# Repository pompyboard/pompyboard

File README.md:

# Wonkle

Wonkle builds gaming hardware such as tablets and keypads for gamers.
Source code, 3D models, schematics, etc. are available under
[OSI-Approved Software and Hardware Licenses](https://opensource.org/licenses). We welcome everyone
to contribute and join us in our quest to make the best hardware for our fellow gamers.

## [Frequently Asked Questions](https://docs.wonkle.io/faq.html)

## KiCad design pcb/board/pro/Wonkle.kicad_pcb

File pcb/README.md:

# PCB

Designed with [KiCad][kicad].

## Manufacturing

Both prototype and production PCB is manufactured by [JLCPCB][jlcpcb].

### Steps

1. Install [KiCad][kicad].
2. Install the [Fabrication Toolkit][fab-toolkit] plugin.
3. "Generate" production files using the plugin with default settings.
4. Go to [jlcpcb.com][jlcpcb] and click "Add gerber file"
5. Select `pcb/production/wonkle.zip`
6. Configure PCB (you will get 5 pcb of which 2 have components soldered)
   - PCB Specifications
     - PCB Thickness - 1.0mm
     - Surface Finish - LeadFree HASL (health is important boiz)
   - High-spec Options
     - Confirm Production file - Yes
     - Mark on PCB - Order Number(Specify Position)
   - PCB Assembly
     - PCBA Qty - minimum is 2
     - Confirm Parts Placement - Yes
     - Advanced
       - Board Cleaning - Yes
7. Press "NEXT"
8. Inspect PCB and press "NEXT" again
9. Upload and process `pcb/production/bom.csv` and `pcb/production/positions.csv`
10. Review the parts and press "NEXT"
11. Fix component placement
    - only J2 (1x4 pin) needs manual edit
12. Select `Research\Education\DIY\Entertainment > DIY Hobby Circuit Board - HS Code 902300` in Quote & Order section. The total price is 137.13 USD as of writing.
13. Press "SAVE TO CART"
14. Select both PCB and PCBA then click "Secure Checkout"
15. Enter shipping info and follow JLCPCB's instruction (e.g. production file confirmation)
16. Wait for a week and you'll receive your very own board!

[kicad]: https://www.kicad.org/
[jlcpcb]: https://jlcpcb.com/
[fab-toolkit]: https://github.com/bennymeg/Fabrication-Toolkit

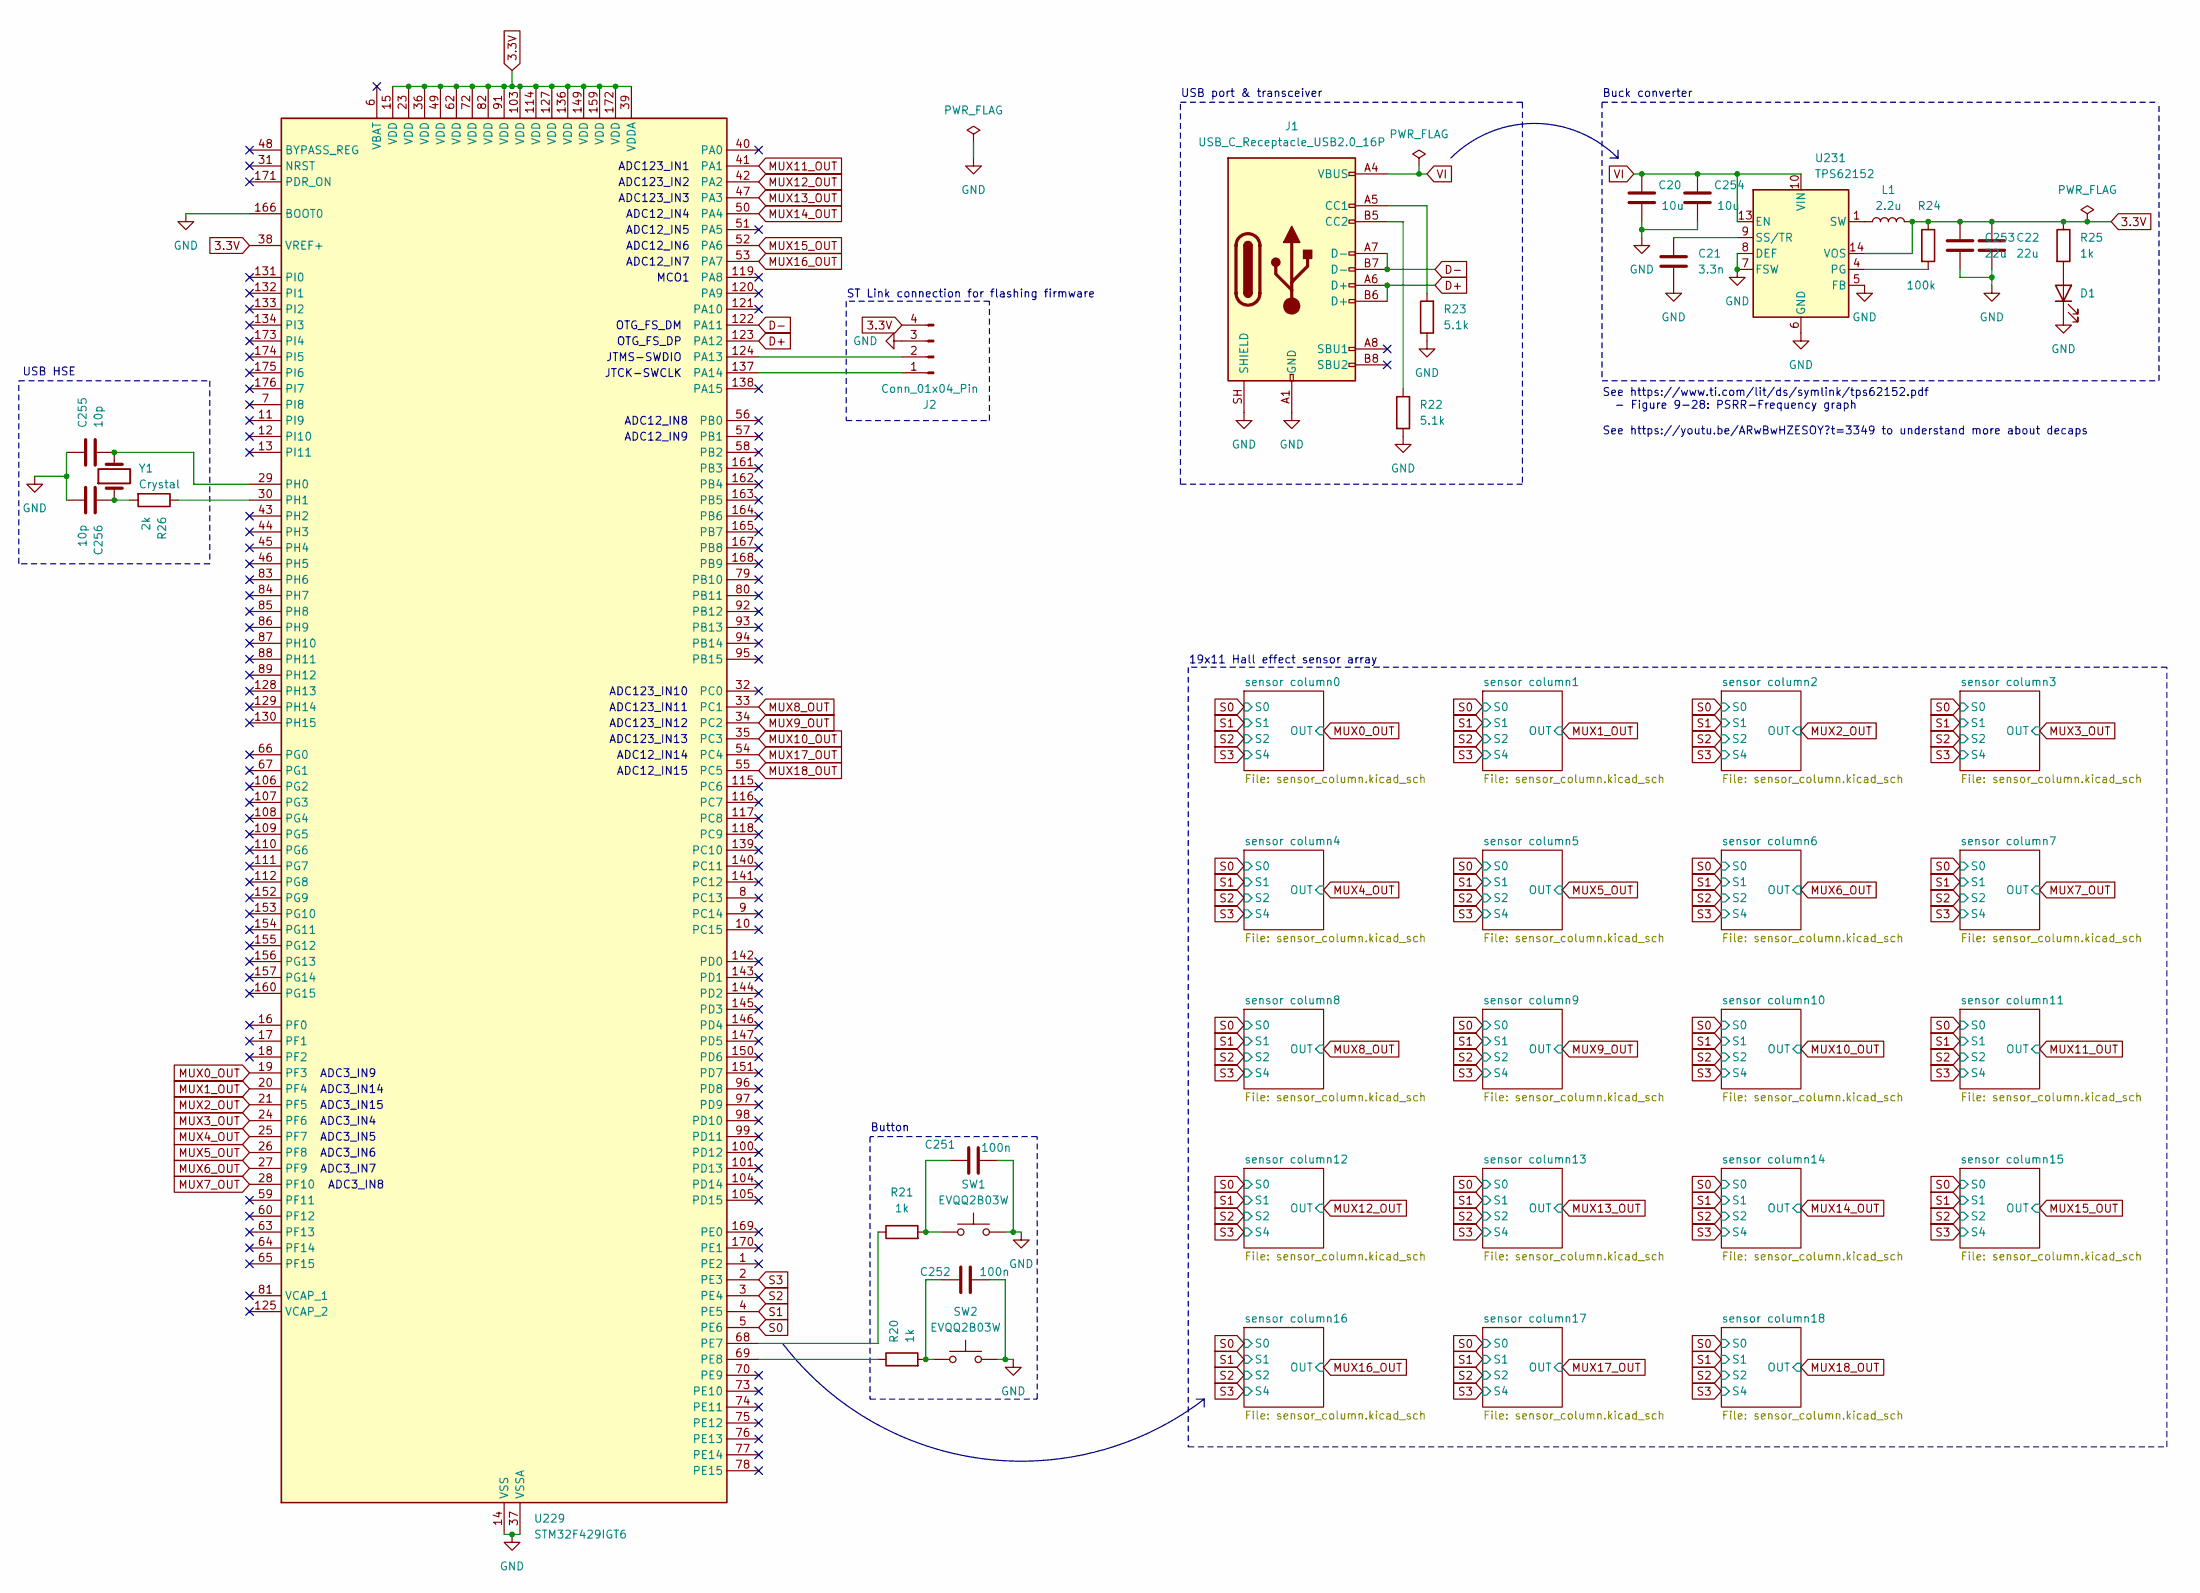
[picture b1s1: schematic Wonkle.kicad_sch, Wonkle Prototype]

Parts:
C20, C254: 10u; C_0402_1005Metric; LCSC Part # C315248
C21: 3.3n; C_0402_1005Metric; LCSC Part # C3881585
C22, C253: 22u; C_0402_1005Metric; LCSC Part # C105226
C251, C252: 100n; C_0402_1005Metric; LCSC Part # C1525
C255, C256: 10p; C_0402_1005Metric; LCSC Part # C1525
D1: F.0603.00139/P2-0603R1TS2-06T-002; LED_0603_1608Metric; LCSC Part # C7496820
J1: USB_C_Receptacle_USB2.0_16P; USB_C_Receptacle_GCT_USB4085; LCSC Part # C7095263
J2: Conn_01x04_Pin; PinHeader_1x04_P2.54mm_Horizontal; LCSC Part # C32713263
L1: 2.2u; L_Coilcraft_XxL4020; LCSC Part # C122469
R20, R21: 1k; R_0402_1005Metric; LCSC Part # C25744
R22, R23: 5.1k; R_0402_1005Metric; LCSC Part # C25905
R24: 100k; R_0603_1608Metric; LCSC Part # C22369815
R25: 1k; R_0402_1005Metric; LCSC Part # C11702
R26: 2k; R_0402_1005Metric; LCSC Part # C11702
SW1, SW2: EVQQ2B03W; SW_SPST_EVQQ2; LCSC Part # C79178
U229: STM32F429IGT6; LQFP-176_24x24mm_P0.5mm
U231: TPS62152; VQFN-16-1EP_3x3mm_P0.5mm_EP1.68x1.68mm_ThermalVias; LCSC Part # C2070611
Y1: Crystal; Crystal_SMD_5032-2Pin_5.0x3.2mm

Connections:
3.3V: C22.1, C253.1, J2.4, L1.2, R24.1, R25.1, U229.15 (VDD), U229.23 (VDD), U229.36 (VDD), U229.38 (VREF+), U229.39 (VDDA), U229.49 (VDD), U229.62 (VDD), U229.72 (VDD), U229.82 (VDD), U229.91 (VDD), U229.103 (VDD), U229.114 (VDD), U229.127 (VDD), U229.136 (VDD), U229.149 (VDD), U229.159 (VDD), U229.172 (VDD), U231.14 (VOS); also elsewhere on the board
D+: J1.A6 (D+), J1.B6 (D+), U229.123 (PA12)
D-: J1.A7 (D-), J1.B7 (D-), U229.122 (PA11)
GND: C20.2, C21.2, C22.2, C251.2, C252.2, C253.2, C254.2, C255.1, C256.2, D1.1 (K), J1.A1 (GND), J1.A12 (GND), J1.B1 (GND), J1.B12 (GND), J1.SH (SHIELD), J2.3, R22.2, R23.1, SW1.2, SW2.2, U229.14 (VSS), U229.22 (VSS), U229.37 (VSSA), U229.61 (VSS), U229.71 (VSS), U229.90 (VSS), U229.102 (VSS), U229.113 (VSS), U229.126 (VSS), U229.135 (VSS), U229.148 (VSS), U229.158 (VSS), U229.166 (BOOT0), U231.5 (FB), U231.6 (GND), U231.7 (FSW), U231.8 (DEF), U231.15 (GND), U231.16 (GND), U231.17 (GND); also elsewhere on the board
MUX0_OUT: U229.19 (PF3); also elsewhere on the board
MUX1_OUT: U229.20 (PF4); also elsewhere on the board
MUX2_OUT: U229.21 (PF5); also elsewhere on the board
MUX3_OUT: U229.24 (PF6); also elsewhere on the board
MUX4_OUT: U229.25 (PF7); also elsewhere on the board
MUX5_OUT: U229.26 (PF8); also elsewhere on the board
MUX6_OUT: U229.27 (PF9); also elsewhere on the board
MUX7_OUT: U229.28 (PF10); also elsewhere on the board
MUX8_OUT: U229.33 (PC1); also elsewhere on the board
MUX9_OUT: U229.34 (PC2); also elsewhere on the board
MUX10_OUT: U229.35 (PC3); also elsewhere on the board
MUX11_OUT: U229.41 (PA1); also elsewhere on the board
MUX12_OUT: U229.42 (PA2); also elsewhere on the board
MUX13_OUT: U229.47 (PA3); also elsewhere on the board
MUX14_OUT: U229.50 (PA4); also elsewhere on the board
MUX15_OUT: U229.52 (PA6); also elsewhere on the board
MUX16_OUT: U229.53 (PA7); also elsewhere on the board
MUX17_OUT: U229.54 (PC4); also elsewhere on the board
MUX18_OUT: U229.55 (PC5); also elsewhere on the board
unnamed: C251.1, R21.2, SW1.1
unnamed: C252.1, R20.2, SW2.1
unnamed: C256.1, R26.2, Y1.1
unnamed: D1.2 (A), R25.2
unnamed: J1.A5 (CC1), R23.2
unnamed: J1.B5 (CC2), R22.1
unnamed: J2.1, U229.137 (PA14)
unnamed: J2.2, U229.124 (PA13)
unnamed: L1.1, U231.1 (SW), U231.2 (SW), U231.3 (SW)
unnamed: R21.1, U229.68 (PE7)
unnamed: R20.1, U229.69 (PE8)
unnamed: C255.2, U229.29 (PH0), Y1.2
unnamed: R26.1, U229.30 (PH1)
unnamed: R24.2, U231.4 (PG)
unnamed: C21.1, U231.9 (SS/TR)
S0: U229.5 (PE6); also elsewhere on the board
S1: U229.4 (PE5); also elsewhere on the board
S2: U229.3 (PE4); also elsewhere on the board
S3: U229.2 (PE3); also elsewhere on the board
VI: C20.1, C254.1, J1.A4 (VBUS), J1.A9 (VBUS), J1.B4 (VBUS), J1.B9 (VBUS), U231.10 (VIN), U231.11 (VIN), U231.12 (VIN), U231.13 (EN)

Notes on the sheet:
ADC3_IN6
ADC3_IN8
ADC12_IN15
ADC3_IN14
ADC12_IN14
ADC123_IN10
ADC123_IN12
Button
ADC12_IN9
ADC3_IN15
OTG_FS_DM
ADC3_IN4
See https://www.ti.com/lit/ds/symlink/tps62152.pdf - Figure 9-28: PSRR-Frequency graph See https://youtu.be/ARwBwHZESOY?t=3349 to understand more about decaps
USB HSE
ADC12_IN4
Buck converter
19x11 Hall effect sensor array
ADC3_IN9
ADC123_IN1
ADC123_IN13
ADC12_IN6
ADC3_IN5
ADC12_IN5
ST Link connection for flashing firmware
JTCK-SWCLK
USB port & transceiver
OTG_FS_DP
MCO1
ADC123_IN11
ADC12_IN8
ADC12_IN7
JTMS-SWDIO
ADC123_IN3
ADC123_IN2
ADC3_IN7

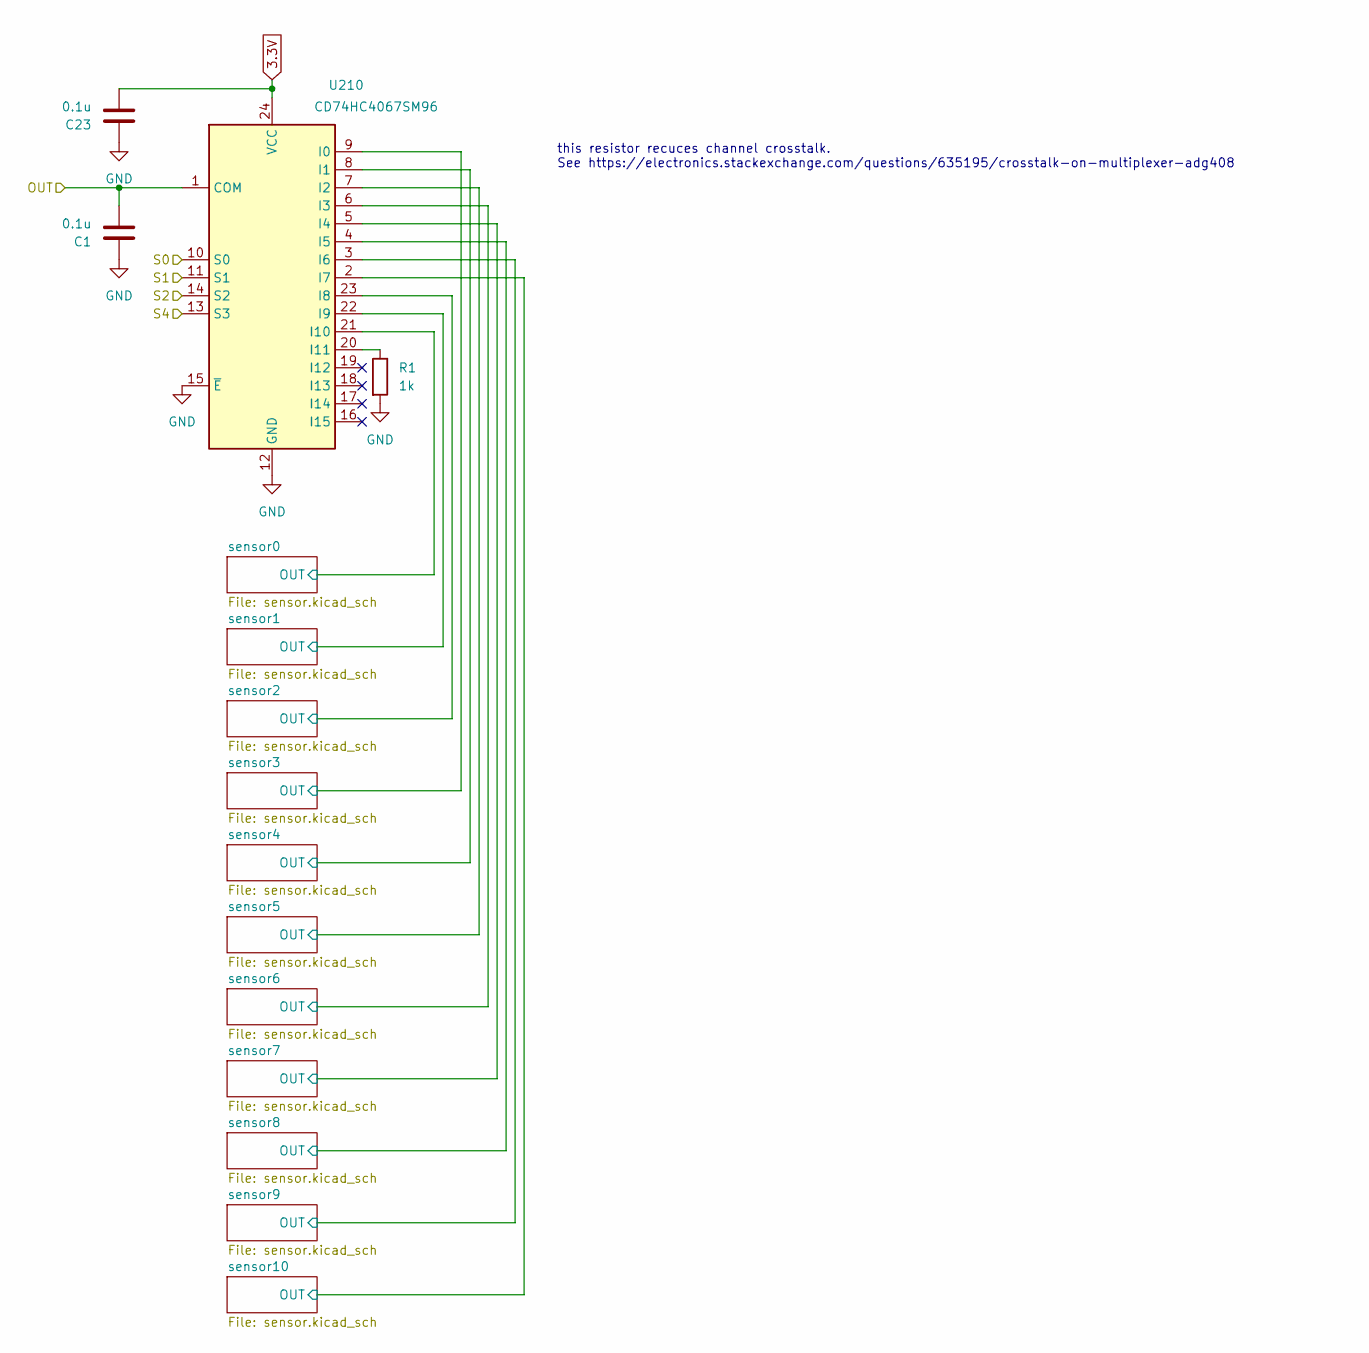
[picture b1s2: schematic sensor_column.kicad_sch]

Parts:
C1, C23: 0.1u; C_0402_1005Metric; LCSC Part # C1525
R1: 1k; R_0402_1005Metric; LCSC Part # C11702
U210: CD74HC4067SM96; SSOP-24_5.3x8.2mm_P0.65mm

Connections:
3.3V: C23.2, U210.24 (VCC); also elsewhere on the board
/sensor column0/sensor0/OUT: U210.21 (I10); also elsewhere on the board
/sensor column0/sensor1/OUT: U210.22 (I9); also elsewhere on the board
/sensor column0/sensor2/OUT: U210.23 (I8); also elsewhere on the board
/sensor column0/sensor3/OUT: U210.9 (I0); also elsewhere on the board
/sensor column0/sensor4/OUT: U210.8 (I1); also elsewhere on the board
/sensor column0/sensor5/OUT: U210.7 (I2); also elsewhere on the board
/sensor column0/sensor6/OUT: U210.6 (I3); also elsewhere on the board
/sensor column0/sensor7/OUT: U210.5 (I4); also elsewhere on the board
/sensor column0/sensor8/OUT: U210.4 (I5); also elsewhere on the board
/sensor column0/sensor9/OUT: U210.3 (I6); also elsewhere on the board
/sensor column0/sensor10/OUT: U210.2 (I7); also elsewhere on the board
GND: C1.1, C23.1, R1.2, U210.12 (GND), U210.15 (~E); also elsewhere on the board
MUX0_OUT: C1.2, U210.1 (COM); also elsewhere on the board
unnamed: R1.1, U210.20 (I11)
S0: U210.10 (S0); also elsewhere on the board
S1: U210.11 (S1); also elsewhere on the board
S2: U210.14 (S2); also elsewhere on the board
S3: U210.13 (S3); also elsewhere on the board

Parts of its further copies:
C2, C3, C4, C5, C6, C7, C8, C9, C10, C11, C12, C13, C14, C15, C16, C17, C18, C19, C24, C25, C26, C27, C28, C29, C30, C31, C32, C33, C34, C35, C36, C37, C38, C39, C40, C41: 0.1u; C_0402_1005Metric; LCSC Part # C1525
R2, R3, R4, R5, R6, R7, R8, R9, R10, R11, R12, R13, R14, R15, R16, R17, R18, R19: 1k; R_0402_1005Metric; LCSC Part # C11702
U211, U212, U213, U214, U215, U216, U217, U218, U219, U220, U221, U222, U223, U224, U225, U226, U227, U228: CD74HC4067SM96; SSOP-24_5.3x8.2mm_P0.65mm

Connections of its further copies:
3.3V: C24.2, C25.2, C26.2, C27.2, C28.2, C29.2, C30.2, C31.2, C32.2, C33.2, C34.2, C35.2, C36.2, C37.2, C38.2, C39.2, C40.2, C41.2, U211.24 (VCC), U212.24 (VCC), U213.24 (VCC), U214.24 (VCC), U215.24 (VCC), U216.24 (VCC), U217.24 (VCC), U218.24 (VCC), U219.24 (VCC), U220.24 (VCC), U221.24 (VCC), U222.24 (VCC), U223.24 (VCC), U224.24 (VCC), U225.24 (VCC), U226.24 (VCC), U227.24 (VCC), U228.24 (VCC); also elsewhere on the board
/sensor column1/sensor0/OUT: U211.21 (I10); also elsewhere on the board
/sensor column1/sensor1/OUT: U211.22 (I9); also elsewhere on the board
/sensor column1/sensor2/OUT: U211.23 (I8); also elsewhere on the board
/sensor column1/sensor3/OUT: U211.9 (I0); also elsewhere on the board
/sensor column1/sensor4/OUT: U211.8 (I1); also elsewhere on the board
/sensor column1/sensor5/OUT: U211.7 (I2); also elsewhere on the board
/sensor column1/sensor6/OUT: U211.6 (I3); also elsewhere on the board
/sensor column1/sensor7/OUT: U211.5 (I4); also elsewhere on the board
/sensor column1/sensor8/OUT: U211.4 (I5); also elsewhere on the board
/sensor column1/sensor9/OUT: U211.3 (I6); also elsewhere on the board
/sensor column1/sensor10/OUT: U211.2 (I7); also elsewhere on the board
/sensor column2/sensor0/OUT: U212.21 (I10); also elsewhere on the board
/sensor column2/sensor1/OUT: U212.22 (I9); also elsewhere on the board
/sensor column2/sensor2/OUT: U212.23 (I8); also elsewhere on the board
/sensor column2/sensor3/OUT: U212.9 (I0); also elsewhere on the board
/sensor column2/sensor4/OUT: U212.8 (I1); also elsewhere on the board
/sensor column2/sensor5/OUT: U212.7 (I2); also elsewhere on the board
/sensor column2/sensor6/OUT: U212.6 (I3); also elsewhere on the board
/sensor column2/sensor7/OUT: U212.5 (I4); also elsewhere on the board
/sensor column2/sensor8/OUT: U212.4 (I5); also elsewhere on the board
/sensor column2/sensor9/OUT: U212.3 (I6); also elsewhere on the board
/sensor column2/sensor10/OUT: U212.2 (I7); also elsewhere on the board
/sensor column3/sensor0/OUT: U213.21 (I10); also elsewhere on the board
/sensor column3/sensor1/OUT: U213.22 (I9); also elsewhere on the board
/sensor column3/sensor2/OUT: U213.23 (I8); also elsewhere on the board
/sensor column3/sensor3/OUT: U213.9 (I0); also elsewhere on the board
/sensor column3/sensor4/OUT: U213.8 (I1); also elsewhere on the board
/sensor column3/sensor5/OUT: U213.7 (I2); also elsewhere on the board
/sensor column3/sensor6/OUT: U213.6 (I3); also elsewhere on the board
/sensor column3/sensor7/OUT: U213.5 (I4); also elsewhere on the board
/sensor column3/sensor8/OUT: U213.4 (I5); also elsewhere on the board
/sensor column3/sensor9/OUT: U213.3 (I6); also elsewhere on the board
/sensor column3/sensor10/OUT: U213.2 (I7); also elsewhere on the board
/sensor column4/sensor0/OUT: U214.21 (I10); also elsewhere on the board
/sensor column4/sensor1/OUT: U214.22 (I9); also elsewhere on the board
/sensor column4/sensor2/OUT: U214.23 (I8); also elsewhere on the board
/sensor column4/sensor3/OUT: U214.9 (I0); also elsewhere on the board
/sensor column4/sensor4/OUT: U214.8 (I1); also elsewhere on the board
/sensor column4/sensor5/OUT: U214.7 (I2); also elsewhere on the board
/sensor column4/sensor6/OUT: U214.6 (I3); also elsewhere on the board
/sensor column4/sensor7/OUT: U214.5 (I4); also elsewhere on the board
/sensor column4/sensor8/OUT: U214.4 (I5); also elsewhere on the board
/sensor column4/sensor9/OUT: U214.3 (I6); also elsewhere on the board
/sensor column4/sensor10/OUT: U214.2 (I7); also elsewhere on the board
/sensor column5/sensor0/OUT: U215.21 (I10); also elsewhere on the board
/sensor column5/sensor1/OUT: U215.22 (I9); also elsewhere on the board
/sensor column5/sensor2/OUT: U215.23 (I8); also elsewhere on the board
/sensor column5/sensor3/OUT: U215.9 (I0); also elsewhere on the board
/sensor column5/sensor4/OUT: U215.8 (I1); also elsewhere on the board
/sensor column5/sensor5/OUT: U215.7 (I2); also elsewhere on the board
/sensor column5/sensor6/OUT: U215.6 (I3); also elsewhere on the board
/sensor column5/sensor7/OUT: U215.5 (I4); also elsewhere on the board
/sensor column5/sensor8/OUT: U215.4 (I5); also elsewhere on the board
/sensor column5/sensor9/OUT: U215.3 (I6); also elsewhere on the board
/sensor column5/sensor10/OUT: U215.2 (I7); also elsewhere on the board
/sensor column6/sensor0/OUT: U216.21 (I10); also elsewhere on the board
/sensor column6/sensor1/OUT: U216.22 (I9); also elsewhere on the board
/sensor column6/sensor2/OUT: U216.23 (I8); also elsewhere on the board
/sensor column6/sensor3/OUT: U216.9 (I0); also elsewhere on the board
/sensor column6/sensor4/OUT: U216.8 (I1); also elsewhere on the board
/sensor column6/sensor5/OUT: U216.7 (I2); also elsewhere on the board
/sensor column6/sensor6/OUT: U216.6 (I3); also elsewhere on the board
/sensor column6/sensor7/OUT: U216.5 (I4); also elsewhere on the board
/sensor column6/sensor8/OUT: U216.4 (I5); also elsewhere on the board
/sensor column6/sensor9/OUT: U216.3 (I6); also elsewhere on the board
/sensor column6/sensor10/OUT: U216.2 (I7); also elsewhere on the board
/sensor column7/sensor0/OUT: U217.21 (I10); also elsewhere on the board
/sensor column7/sensor1/OUT: U217.22 (I9); also elsewhere on the board
/sensor column7/sensor2/OUT: U217.23 (I8); also elsewhere on the board
/sensor column7/sensor3/OUT: U217.9 (I0); also elsewhere on the board
/sensor column7/sensor4/OUT: U217.8 (I1); also elsewhere on the board
/sensor column7/sensor5/OUT: U217.7 (I2); also elsewhere on the board
/sensor column7/sensor6/OUT: U217.6 (I3); also elsewhere on the board
/sensor column7/sensor7/OUT: U217.5 (I4); also elsewhere on the board
/sensor column7/sensor8/OUT: U217.4 (I5); also elsewhere on the board
/sensor column7/sensor9/OUT: U217.3 (I6); also elsewhere on the board
/sensor column7/sensor10/OUT: U217.2 (I7); also elsewhere on the board
/sensor column8/sensor0/OUT: U218.21 (I10); also elsewhere on the board
/sensor column8/sensor1/OUT: U218.22 (I9); also elsewhere on the board
/sensor column8/sensor2/OUT: U218.23 (I8); also elsewhere on the board
/sensor column8/sensor3/OUT: U218.9 (I0); also elsewhere on the board
/sensor column8/sensor4/OUT: U218.8 (I1); also elsewhere on the board
/sensor column8/sensor5/OUT: U218.7 (I2); also elsewhere on the board
/sensor column8/sensor6/OUT: U218.6 (I3); also elsewhere on the board
/sensor column8/sensor7/OUT: U218.5 (I4); also elsewhere on the board
/sensor column8/sensor8/OUT: U218.4 (I5); also elsewhere on the board
/sensor column8/sensor9/OUT: U218.3 (I6); also elsewhere on the board
/sensor column8/sensor10/OUT: U218.2 (I7); also elsewhere on the board
/sensor column9/sensor0/OUT: U219.21 (I10); also elsewhere on the board
/sensor column9/sensor1/OUT: U219.22 (I9); also elsewhere on the board
/sensor column9/sensor2/OUT: U219.23 (I8); also elsewhere on the board
/sensor column9/sensor3/OUT: U219.9 (I0); also elsewhere on the board
/sensor column9/sensor4/OUT: U219.8 (I1); also elsewhere on the board
/sensor column9/sensor5/OUT: U219.7 (I2); also elsewhere on the board
/sensor column9/sensor6/OUT: U219.6 (I3); also elsewhere on the board
/sensor column9/sensor7/OUT: U219.5 (I4); also elsewhere on the board
/sensor column9/sensor8/OUT: U219.4 (I5); also elsewhere on the board
/sensor column9/sensor9/OUT: U219.3 (I6); also elsewhere on the board
/sensor column9/sensor10/OUT: U219.2 (I7); also elsewhere on the board
/sensor column10/sensor0/OUT: U220.21 (I10); also elsewhere on the board
/sensor column10/sensor1/OUT: U220.22 (I9); also elsewhere on the board
/sensor column10/sensor2/OUT: U220.23 (I8); also elsewhere on the board
/sensor column10/sensor3/OUT: U220.9 (I0); also elsewhere on the board
/sensor column10/sensor4/OUT: U220.8 (I1); also elsewhere on the board
/sensor column10/sensor5/OUT: U220.7 (I2); also elsewhere on the board
/sensor column10/sensor6/OUT: U220.6 (I3); also elsewhere on the board
/sensor column10/sensor7/OUT: U220.5 (I4); also elsewhere on the board
/sensor column10/sensor8/OUT: U220.4 (I5); also elsewhere on the board
/sensor column10/sensor9/OUT: U220.3 (I6); also elsewhere on the board
/sensor column10/sensor10/OUT: U220.2 (I7); also elsewhere on the board
/sensor column11/sensor0/OUT: U221.21 (I10); also elsewhere on the board
/sensor column11/sensor1/OUT: U221.22 (I9); also elsewhere on the board
/sensor column11/sensor2/OUT: U221.23 (I8); also elsewhere on the board
/sensor column11/sensor3/OUT: U221.9 (I0); also elsewhere on the board
/sensor column11/sensor4/OUT: U221.8 (I1); also elsewhere on the board
/sensor column11/sensor5/OUT: U221.7 (I2); also elsewhere on the board
/sensor column11/sensor6/OUT: U221.6 (I3); also elsewhere on the board
/sensor column11/sensor7/OUT: U221.5 (I4); also elsewhere on the board
/sensor column11/sensor8/OUT: U221.4 (I5); also elsewhere on the board
/sensor column11/sensor9/OUT: U221.3 (I6); also elsewhere on the board
/sensor column11/sensor10/OUT: U221.2 (I7); also elsewhere on the board
/sensor column12/sensor0/OUT: U222.21 (I10); also elsewhere on the board
/sensor column12/sensor1/OUT: U222.22 (I9); also elsewhere on the board
/sensor column12/sensor2/OUT: U222.23 (I8); also elsewhere on the board
/sensor column12/sensor3/OUT: U222.9 (I0); also elsewhere on the board
/sensor column12/sensor4/OUT: U222.8 (I1); also elsewhere on the board
/sensor column12/sensor5/OUT: U222.7 (I2); also elsewhere on the board
/sensor column12/sensor6/OUT: U222.6 (I3); also elsewhere on the board
/sensor column12/sensor7/OUT: U222.5 (I4); also elsewhere on the board
/sensor column12/sensor8/OUT: U222.4 (I5); also elsewhere on the board
/sensor column12/sensor9/OUT: U222.3 (I6); also elsewhere on the board
/sensor column12/sensor10/OUT: U222.2 (I7); also elsewhere on the board
/sensor column13/sensor0/OUT: U223.21 (I10); also elsewhere on the board
/sensor column13/sensor1/OUT: U223.22 (I9); also elsewhere on the board
/sensor column13/sensor2/OUT: U223.23 (I8); also elsewhere on the board
/sensor column13/sensor3/OUT: U223.9 (I0); also elsewhere on the board
/sensor column13/sensor4/OUT: U223.8 (I1); also elsewhere on the board
/sensor column13/sensor5/OUT: U223.7 (I2); also elsewhere on the board
/sensor column13/sensor6/OUT: U223.6 (I3); also elsewhere on the board
/sensor column13/sensor7/OUT: U223.5 (I4); also elsewhere on the board
/sensor column13/sensor8/OUT: U223.4 (I5); also elsewhere on the board
/sensor column13/sensor9/OUT: U223.3 (I6); also elsewhere on the board
/sensor column13/sensor10/OUT: U223.2 (I7); also elsewhere on the board
/sensor column14/sensor0/OUT: U224.21 (I10); also elsewhere on the board
/sensor column14/sensor1/OUT: U224.22 (I9); also elsewhere on the board
/sensor column14/sensor2/OUT: U224.23 (I8); also elsewhere on the board
/sensor column14/sensor3/OUT: U224.9 (I0); also elsewhere on the board
/sensor column14/sensor4/OUT: U224.8 (I1); also elsewhere on the board
/sensor column14/sensor5/OUT: U224.7 (I2); also elsewhere on the board
/sensor column14/sensor6/OUT: U224.6 (I3); also elsewhere on the board
/sensor column14/sensor7/OUT: U224.5 (I4); also elsewhere on the board
/sensor column14/sensor8/OUT: U224.4 (I5); also elsewhere on the board
/sensor column14/sensor9/OUT: U224.3 (I6); also elsewhere on the board
/sensor column14/sensor10/OUT: U224.2 (I7); also elsewhere on the board
/sensor column15/sensor0/OUT: U225.21 (I10); also elsewhere on the board
/sensor column15/sensor1/OUT: U225.22 (I9); also elsewhere on the board
/sensor column15/sensor2/OUT: U225.23 (I8); also elsewhere on the board
/sensor column15/sensor3/OUT: U225.9 (I0); also elsewhere on the board
/sensor column15/sensor4/OUT: U225.8 (I1); also elsewhere on the board
/sensor column15/sensor5/OUT: U225.7 (I2); also elsewhere on the board
/sensor column15/sensor6/OUT: U225.6 (I3); also elsewhere on the board
/sensor column15/sensor7/OUT: U225.5 (I4); also elsewhere on the board
/sensor column15/sensor8/OUT: U225.4 (I5); also elsewhere on the board
/sensor column15/sensor9/OUT: U225.3 (I6); also elsewhere on the board
/sensor column15/sensor10/OUT: U225.2 (I7); also elsewhere on the board
/sensor column16/sensor0/OUT: U226.21 (I10); also elsewhere on the board
/sensor column16/sensor1/OUT: U226.22 (I9); also elsewhere on the board
/sensor column16/sensor2/OUT: U226.23 (I8); also elsewhere on the board
/sensor column16/sensor3/OUT: U226.9 (I0); also elsewhere on the board
/sensor column16/sensor4/OUT: U226.8 (I1); also elsewhere on the board
/sensor column16/sensor5/OUT: U226.7 (I2); also elsewhere on the board
/sensor column16/sensor6/OUT: U226.6 (I3); also elsewhere on the board
/sensor column16/sensor7/OUT: U226.5 (I4); also elsewhere on the board
/sensor column16/sensor8/OUT: U226.4 (I5); also elsewhere on the board
/sensor column16/sensor9/OUT: U226.3 (I6); also elsewhere on the board
/sensor column16/sensor10/OUT: U226.2 (I7); also elsewhere on the board
/sensor column17/sensor0/OUT: U227.21 (I10); also elsewhere on the board
/sensor column17/sensor1/OUT: U227.22 (I9); also elsewhere on the board
/sensor column17/sensor2/OUT: U227.23 (I8); also elsewhere on the board
/sensor column17/sensor3/OUT: U227.9 (I0); also elsewhere on the board
/sensor column17/sensor4/OUT: U227.8 (I1); also elsewhere on the board
/sensor column17/sensor5/OUT: U227.7 (I2); also elsewhere on the board
/sensor column17/sensor6/OUT: U227.6 (I3); also elsewhere on the board
/sensor column17/sensor7/OUT: U227.5 (I4); also elsewhere on the board
/sensor column17/sensor8/OUT: U227.4 (I5); also elsewhere on the board
/sensor column17/sensor9/OUT: U227.3 (I6); also elsewhere on the board
/sensor column17/sensor10/OUT: U227.2 (I7); also elsewhere on the board
/sensor column18/sensor0/OUT: U228.21 (I10); also elsewhere on the board
/sensor column18/sensor1/OUT: U228.22 (I9); also elsewhere on the board
/sensor column18/sensor2/OUT: U228.23 (I8); also elsewhere on the board
/sensor column18/sensor3/OUT: U228.9 (I0); also elsewhere on the board
/sensor column18/sensor4/OUT: U228.8 (I1); also elsewhere on the board
/sensor column18/sensor5/OUT: U228.7 (I2); also elsewhere on the board
/sensor column18/sensor6/OUT: U228.6 (I3); also elsewhere on the board
/sensor column18/sensor7/OUT: U228.5 (I4); also elsewhere on the board
/sensor column18/sensor8/OUT: U228.4 (I5); also elsewhere on the board
/sensor column18/sensor9/OUT: U228.3 (I6); also elsewhere on the board
/sensor column18/sensor10/OUT: U228.2 (I7); also elsewhere on the board
GND: C2.1, C3.1, C4.1, C5.1, C6.1, C7.1, C8.1, C9.1, C10.1, C11.1, C12.1, C13.1, C14.1, C15.1, C16.1, C17.1, C18.1, C19.1, C24.1, C25.1, C26.1, C27.1, C28.1, C29.1, C30.1, C31.1, C32.1, C33.1, C34.1, C35.1, C36.1, C37.1, C38.1, C39.1, C40.1, C41.1, R2.2, R3.2, R4.2, R5.2, R6.2, R7.2, R8.2, R9.2, R10.2, R11.2, R12.2, R13.2, R14.2, R15.2, R16.2, R17.2, R18.2, R19.2, U211.12 (GND), U211.15 (~E), U212.12 (GND), U212.15 (~E), U213.12 (GND), U213.15 (~E), U214.12 (GND), U214.15 (~E), U215.12 (GND), U215.15 (~E), U216.12 (GND), U216.15 (~E), U217.12 (GND), U217.15 (~E), U218.12 (GND), U218.15 (~E), U219.12 (GND), U219.15 (~E), U220.12 (GND), U220.15 (~E), U221.12 (GND), U221.15 (~E), U222.12 (GND), U222.15 (~E), U223.12 (GND), U223.15 (~E), U224.12 (GND), U224.15 (~E), U225.12 (GND), U225.15 (~E), U226.12 (GND), U226.15 (~E), U227.12 (GND), U227.15 (~E), U228.12 (GND), U228.15 (~E); also elsewhere on the board
MUX1_OUT: C2.2, U211.1 (COM); also elsewhere on the board
MUX2_OUT: C3.2, U212.1 (COM); also elsewhere on the board
MUX3_OUT: C4.2, U213.1 (COM); also elsewhere on the board
MUX4_OUT: C5.2, U214.1 (COM); also elsewhere on the board
MUX5_OUT: C6.2, U215.1 (COM); also elsewhere on the board
MUX6_OUT: C7.2, U216.1 (COM); also elsewhere on the board
MUX7_OUT: C8.2, U217.1 (COM); also elsewhere on the board
MUX8_OUT: C9.2, U218.1 (COM); also elsewhere on the board
MUX9_OUT: C10.2, U219.1 (COM); also elsewhere on the board
MUX10_OUT: C11.2, U220.1 (COM); also elsewhere on the board
MUX11_OUT: C12.2, U221.1 (COM); also elsewhere on the board
MUX12_OUT: C13.2, U222.1 (COM); also elsewhere on the board
MUX13_OUT: C14.2, U223.1 (COM); also elsewhere on the board
MUX14_OUT: C15.2, U224.1 (COM); also elsewhere on the board
MUX15_OUT: C16.2, U225.1 (COM); also elsewhere on the board
MUX16_OUT: C17.2, U226.1 (COM); also elsewhere on the board
MUX17_OUT: C18.2, U227.1 (COM); also elsewhere on the board
MUX18_OUT: C19.2, U228.1 (COM); also elsewhere on the board
unnamed: R2.1, U211.20 (I11)
unnamed: R3.1, U212.20 (I11)
unnamed: R4.1, U213.20 (I11)
unnamed: R5.1, U214.20 (I11)
unnamed: R6.1, U215.20 (I11)
unnamed: R7.1, U216.20 (I11)
unnamed: R8.1, U217.20 (I11)
unnamed: R9.1, U218.20 (I11)
unnamed: R10.1, U219.20 (I11)
unnamed: R11.1, U220.20 (I11)
unnamed: R12.1, U221.20 (I11)
unnamed: R13.1, U222.20 (I11)
unnamed: R14.1, U223.20 (I11)
unnamed: R15.1, U224.20 (I11)
unnamed: R16.1, U225.20 (I11)
unnamed: R17.1, U226.20 (I11)
unnamed: R18.1, U227.20 (I11)
unnamed: R19.1, U228.20 (I11)
S0: U211.10 (S0), U212.10 (S0), U213.10 (S0), U214.10 (S0), U215.10 (S0), U216.10 (S0), U217.10 (S0), U218.10 (S0), U219.10 (S0), U220.10 (S0), U221.10 (S0), U222.10 (S0), U223.10 (S0), U224.10 (S0), U225.10 (S0), U226.10 (S0), U227.10 (S0), U228.10 (S0); also elsewhere on the board
S1: U211.11 (S1), U212.11 (S1), U213.11 (S1), U214.11 (S1), U215.11 (S1), U216.11 (S1), U217.11 (S1), U218.11 (S1), U219.11 (S1), U220.11 (S1), U221.11 (S1), U222.11 (S1), U223.11 (S1), U224.11 (S1), U225.11 (S1), U226.11 (S1), U227.11 (S1), U228.11 (S1); also elsewhere on the board
S2: U211.14 (S2), U212.14 (S2), U213.14 (S2), U214.14 (S2), U215.14 (S2), U216.14 (S2), U217.14 (S2), U218.14 (S2), U219.14 (S2), U220.14 (S2), U221.14 (S2), U222.14 (S2), U223.14 (S2), U224.14 (S2), U225.14 (S2), U226.14 (S2), U227.14 (S2), U228.14 (S2); also elsewhere on the board
S3: U211.13 (S3), U212.13 (S3), U213.13 (S3), U214.13 (S3), U215.13 (S3), U216.13 (S3), U217.13 (S3), U218.13 (S3), U219.13 (S3), U220.13 (S3), U221.13 (S3), U222.13 (S3), U223.13 (S3), U224.13 (S3), U225.13 (S3), U226.13 (S3), U227.13 (S3), U228.13 (S3); also elsewhere on the board

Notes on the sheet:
this resistor recuces channel crosstalk. See https://electronics.stackexchange.com/questions/635195/crosstalk-on-multiplexer-adg408
